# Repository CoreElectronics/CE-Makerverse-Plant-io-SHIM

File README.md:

# Makerverse Plant_io SHIM

This is the repo for the Core Electronics [Makerverse Plant_io SHIM](https://core-electronics.com.au/catalog/product/view/sku/CE09594).

## License
This project is open source - please review the LICENSE.md file for further licensing information.

If you have any technical questions, or concerns about licensing, please contact technical support on the [Core Electronics forums](https://forum.core-electronics.com.au/).

*\"Makerverse\" and the Makerverse logo are trademarks of Core Electronics Pty Ltd.*

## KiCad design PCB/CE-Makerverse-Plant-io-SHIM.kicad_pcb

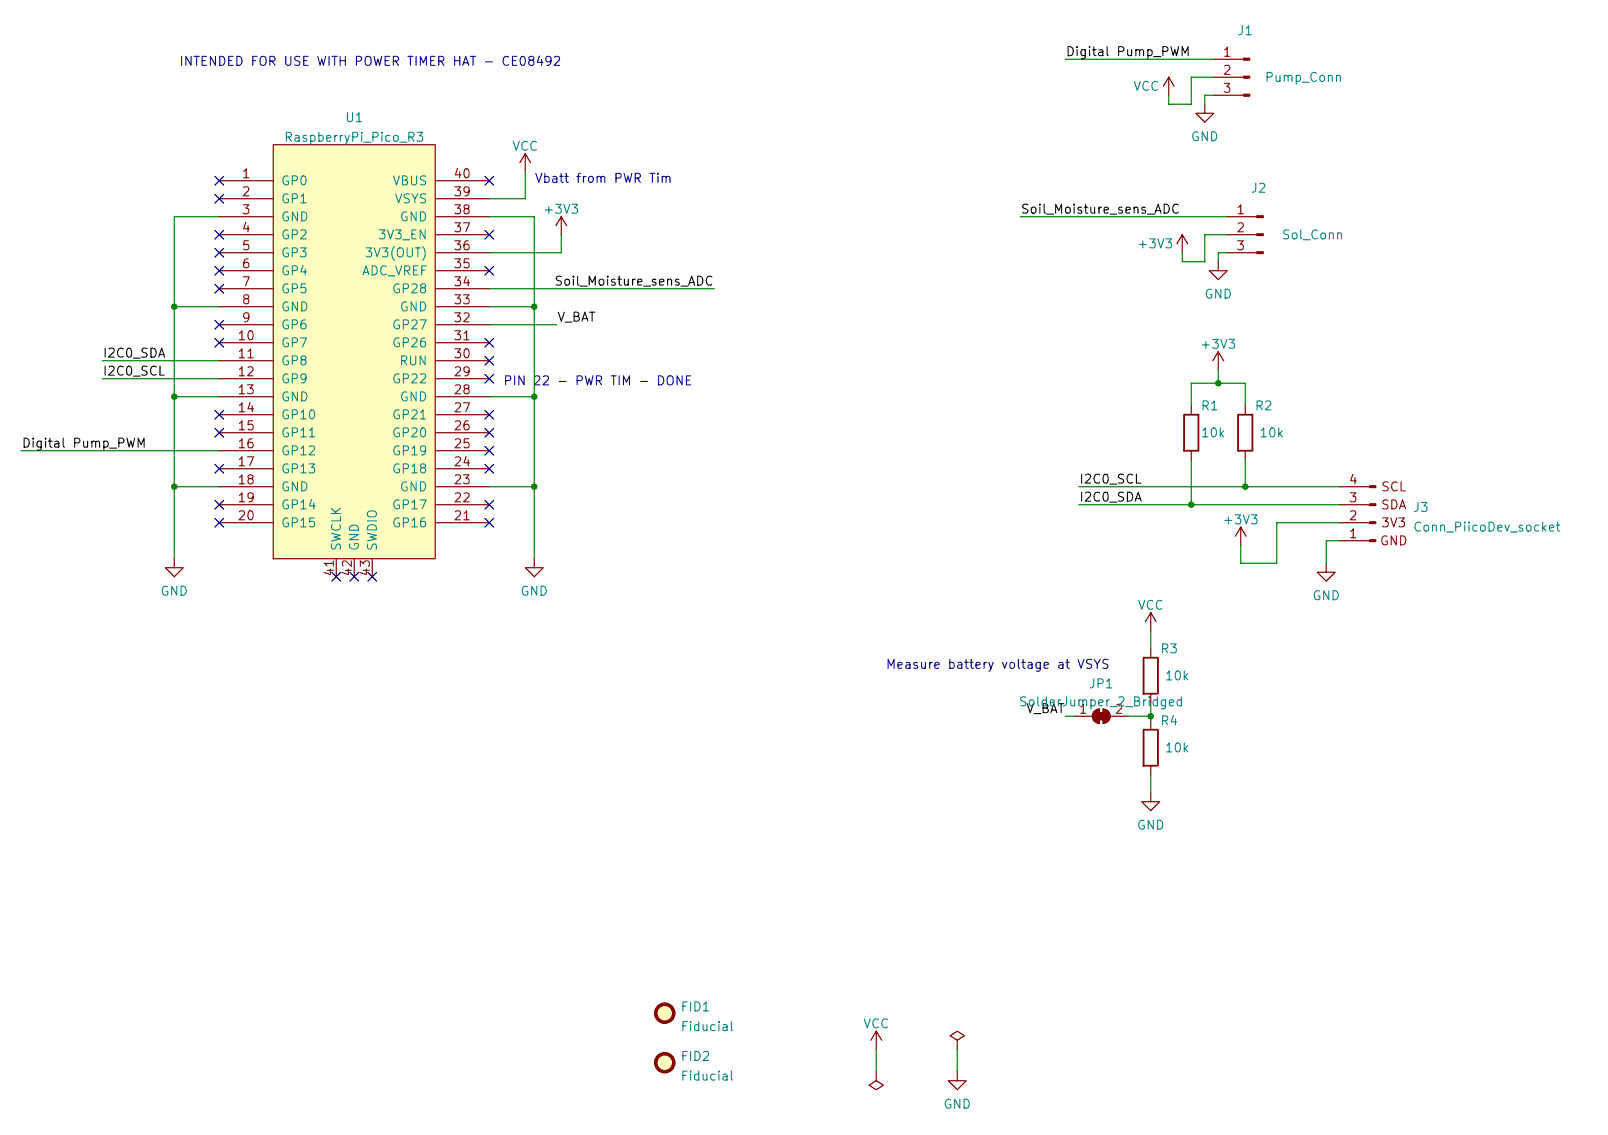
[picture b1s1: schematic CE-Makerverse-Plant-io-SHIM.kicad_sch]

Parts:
FID1, FID2: Fiducial; Fiducial_1mm_Mask2mm
J1: Pump_Conn; PinHeader_1x03_P2.54mm_Vertical_SMD_Pin1Left-BetterMechanic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
J2: Sol_Conn; PinHeader_1x03_P2.54mm_Vertical_SMD_Pin1Left-BetterMechanic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
J3: Conn_PiicoDev_socket; JST_SH_SM04B-SRSS-TB_1x04-1MP_P1.00mm_Horizontal
JP1: SolderJumper_2_Bridged; SolderJumper-2_P1.3mm_Bridged_RoundedPad1.0x1.5mm
R1, R2, R3, R4: 10k; R_0402_1005Metric
U1: RaspberryPi_Pico_R3; Pico-Shim-Fit_Oval-Spark

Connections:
+3V3: J2.2, J3.2, R1.1, R2.1, U1.36 (3V3(OUT))
/Digital Pump_PWM: J1.1, U1.16 (GP12)
/I2C0_SCL: J3.4, R2.2, U1.12 (GP9)
/I2C0_SDA: J3.3, R1.2, U1.11 (GP8)
/Soil_Moisture_sens_ADC: J2.1, U1.34 (GP28)
/V_BAT: JP1.1 (A), U1.32 (GP27)
GND: J1.3, J2.3, J3.1, R4.2, U1.3 (GND), U1.8 (GND), U1.13 (GND), U1.18 (GND), U1.23 (GND), U1.28 (GND), U1.33 (GND), U1.38 (GND)
unnamed: JP1.2 (B), R3.2, R4.1
VCC: J1.2, R3.1, U1.39 (VSYS)

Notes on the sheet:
INTENDED FOR USE WITH POWER TIMER HAT - CE08492
Vbatt from PWR Tim
PIN 22 - PWR TIM - DONE
Measure battery voltage at VSYS

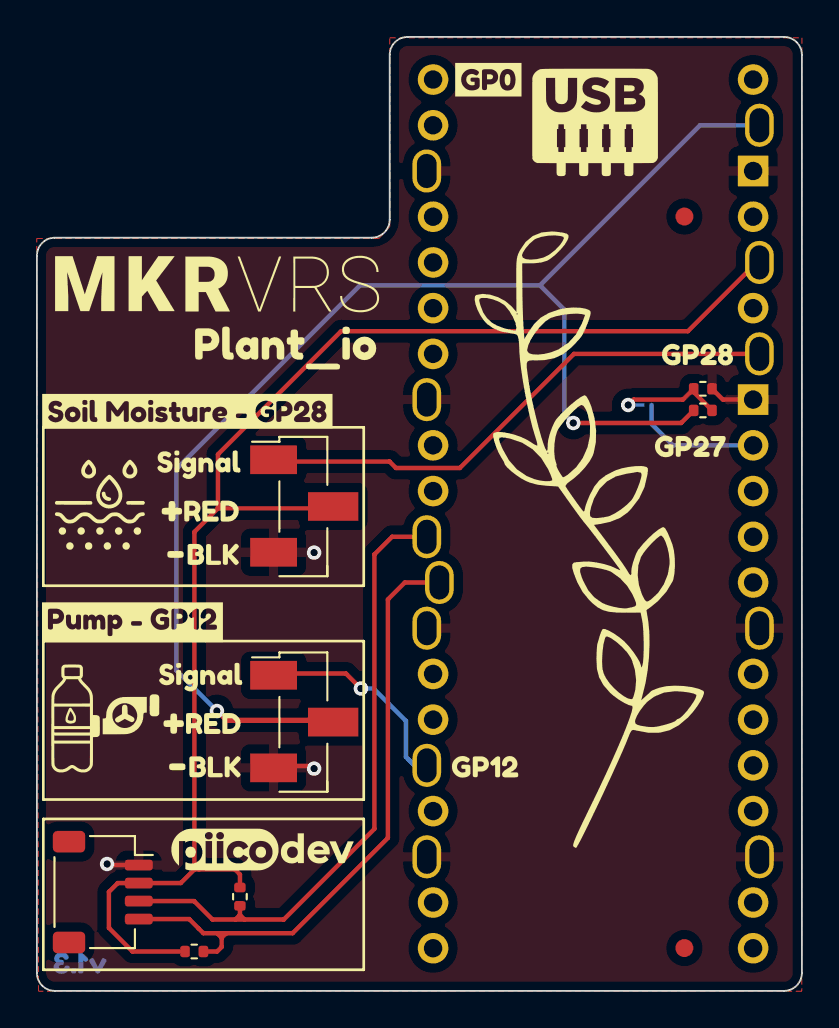
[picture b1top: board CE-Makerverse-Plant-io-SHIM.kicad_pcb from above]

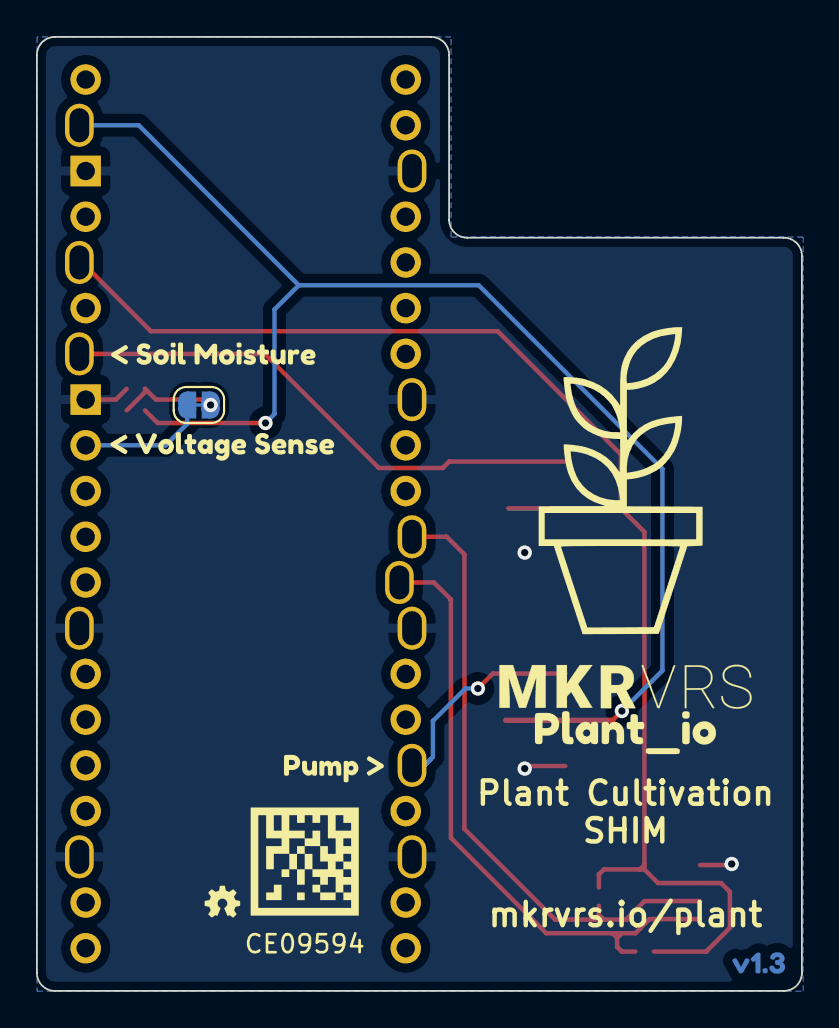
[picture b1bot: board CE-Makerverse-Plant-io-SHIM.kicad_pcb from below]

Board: 2 copper layers, 42.5 x 53.0 mm, 33 parts (6 on the bottom side), 9 nets.

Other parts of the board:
kibuzzard-63FC05E1: G***; kibuzzard-63FC05E1
kibuzzard-63FC007A: G***; kibuzzard-63FC007A
kibuzzard-63FC0833: G***; kibuzzard-63FC0833
kibuzzard-63FE8B61, kibuzzard-63FE8B61#2: G***; kibuzzard-63FE8B61
kibuzzard-64251D2A: G***; kibuzzard-64251D2A
kibuzzard-64251DB8: G***; kibuzzard-64251DB8
kibuzzard-642511A6: G***; kibuzzard-642511A6
kibuzzard-642512E6, kibuzzard-642512E6#2: G***; kibuzzard-642512E6
kibuzzard-642512F4, kibuzzard-642512F4#2: G***; kibuzzard-642512F4
kibuzzard-642514F3: G***; kibuzzard-642514F3
kibuzzard-6425130D, kibuzzard-6425130D#2: G***; kibuzzard-6425130D
kibuzzard-64251220: G***; kibuzzard-64251220
kibuzzard-64251322, kibuzzard-64251322#2: G***; kibuzzard-64251322
kibuzzard-64251367, kibuzzard-64251367#2: G***; kibuzzard-64251367
kibuzzard-64251509: G***; kibuzzard-64251509
kibuzzard-64251517: G***; kibuzzard-64251517

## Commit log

2023-03-30 initial commit v1.3
2023-03-30 v1.3 fix minor edge cut and fill
